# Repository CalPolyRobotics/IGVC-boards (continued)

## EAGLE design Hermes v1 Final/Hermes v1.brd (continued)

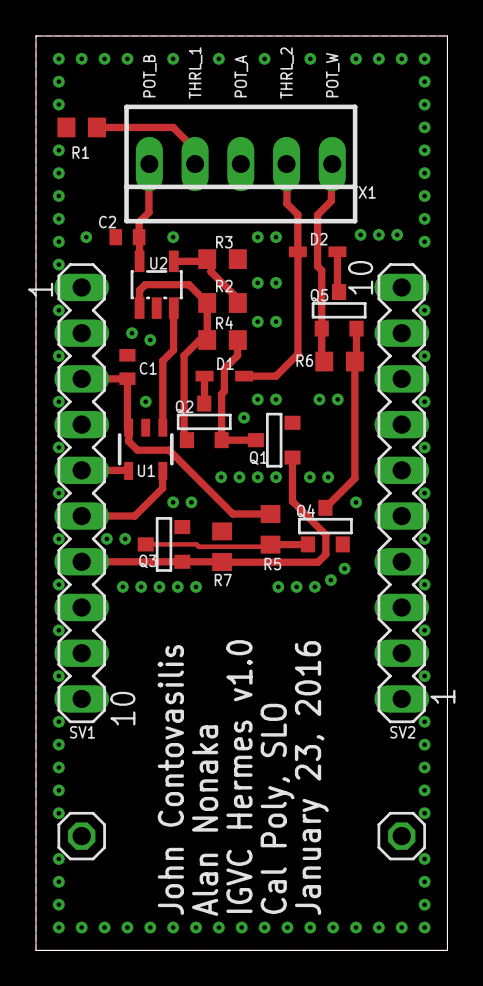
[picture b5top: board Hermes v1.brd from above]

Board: 2 copper layers, 22.9 x 50.8 mm, 23 parts (0 on the bottom side), 17 nets.

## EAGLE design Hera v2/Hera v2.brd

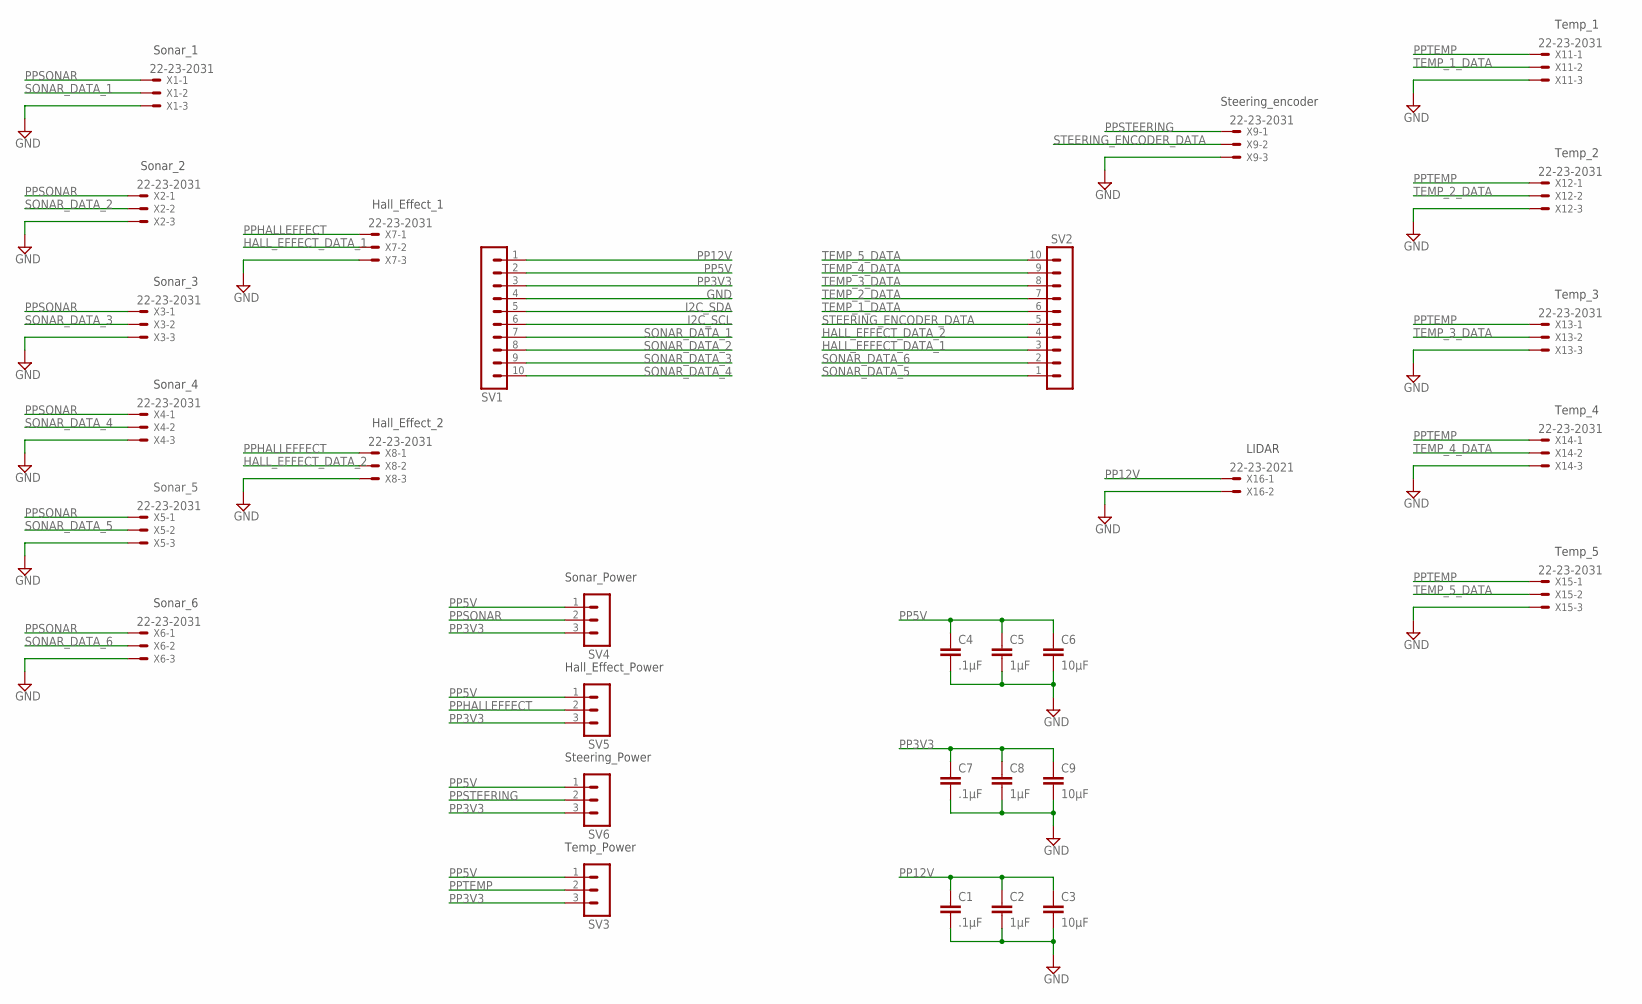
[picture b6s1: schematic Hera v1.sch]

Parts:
C1, C4, C7: .1µF; C0402; DIGI 490-5920-1-ND
C2, C5, C8: 1µF; C0603; DIGI 490-3897-1-ND
C3, C6, C9: 10µF; C1206; DIGI 490-5525-1-ND
SV1, SV2: MA10-1
SV3, SV4, SV5, SV6: MA03-1
X1, X2, X3, X4, X5, X6, X7, X8, X9, X11, X12, X13, X14, X15: 22-23-2031
X16: 22-23-2021

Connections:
GND: C1.2, C2.2, C3.2, C4.2, C5.2, C6.2, C7.2, C8.2, C9.2, SV1.4, X1.3, X2.3, X3.3, X4.3, X5.3, X6.3, X7.3, X8.3, X9.3, X11.3, X12.3, X13.3, X14.3, X15.3, X16.2
HALL_EFFECT_DATA_1: SV2.3, X7.2
HALL_EFFECT_DATA_2: SV2.4, X8.2
I2C_SCL: SV1.6
I2C_SDA: SV1.5
PP3V3: C7.1, C8.1, C9.1, SV1.3, SV3.3, SV4.3, SV5.3, SV6.3
PP5V: C4.1, C5.1, C6.1, SV1.2, SV3.1, SV4.1, SV5.1, SV6.1
PP12V: C1.1, C2.1, C3.1, SV1.1, X16.1
PPHALLEFFECT: SV5.2, X7.1, X8.1
PPSONAR: SV4.2, X1.1, X2.1, X3.1, X4.1, X5.1, X6.1
PPSTEERING: SV6.2, X9.1
PPTEMP: SV3.2, X11.1, X12.1, X13.1, X14.1, X15.1
SONAR_DATA_1: SV1.7, X1.2
SONAR_DATA_2: SV1.8, X2.2
SONAR_DATA_3: SV1.9, X3.2
SONAR_DATA_4: SV1.10, X4.2
SONAR_DATA_5: SV2.1, X5.2
SONAR_DATA_6: SV2.2, X6.2
STEERING_ENCODER_DATA: SV2.5, X9.2
TEMP_1_DATA: SV2.6, X11.2
TEMP_2_DATA: SV2.7, X12.2
TEMP_3_DATA: SV2.8, X13.2
TEMP_4_DATA: SV2.9, X14.2
TEMP_5_DATA: SV2.10, X15.2

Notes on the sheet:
Sonar_1
Sonar_2
Sonar_3
Sonar_4
Sonar_5
Sonar_6
Hall_Effect_1
Hall_Effect_2
Steering_encoder
Temp_1
Temp_2
Temp_3
Temp_4
Temp_5
LIDAR
Sonar_Power
Hall_Effect_Power
Steering_Power
Temp_Power

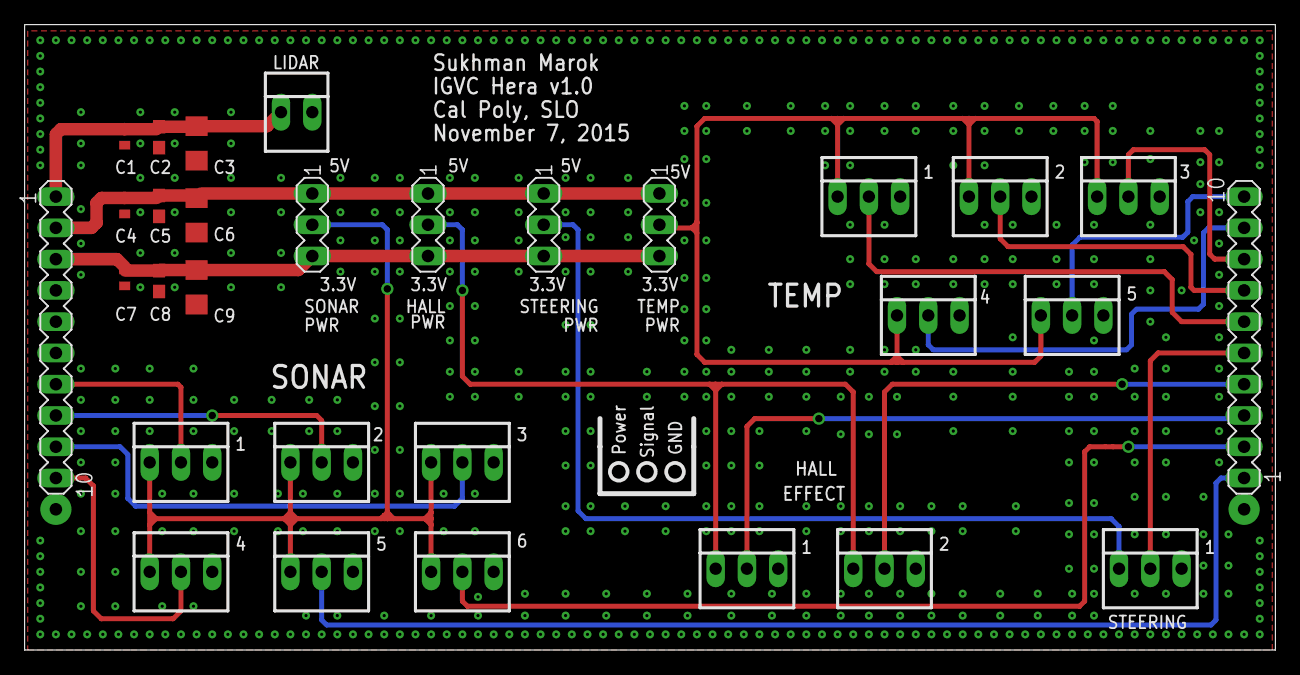
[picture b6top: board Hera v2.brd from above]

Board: 2 copper layers, 101.6 x 50.8 mm, 30 parts (0 on the bottom side), 22 nets.

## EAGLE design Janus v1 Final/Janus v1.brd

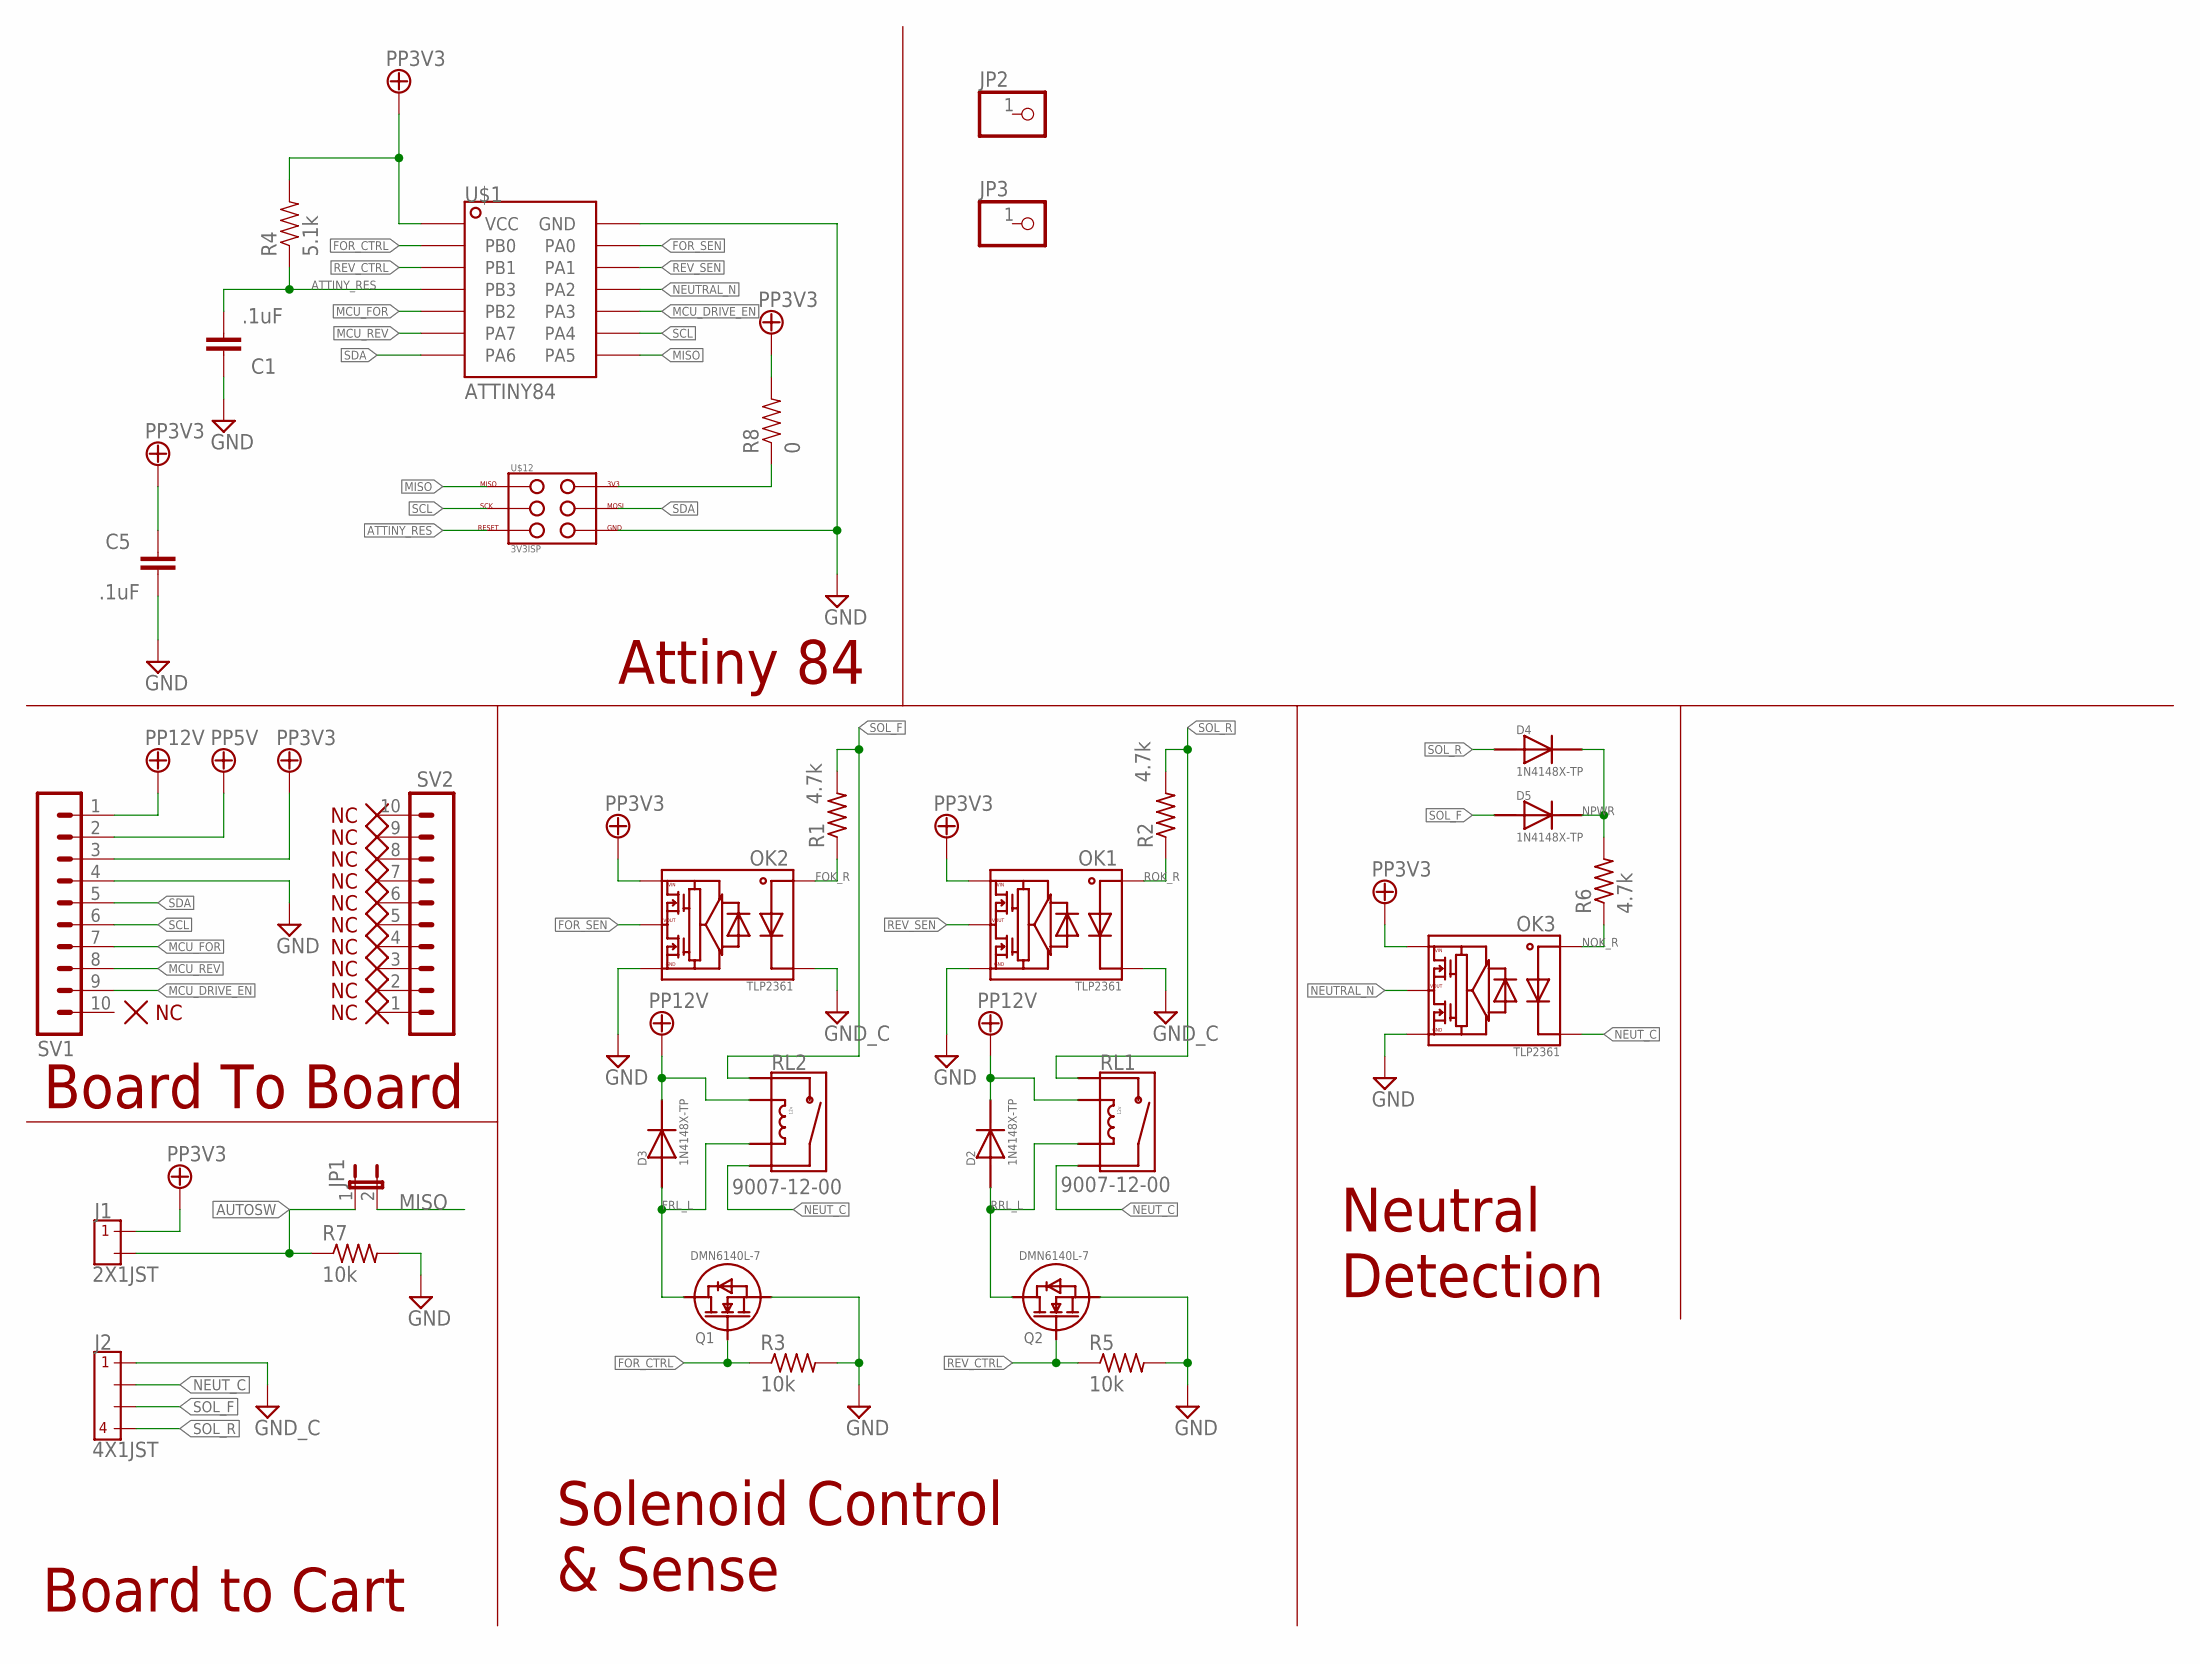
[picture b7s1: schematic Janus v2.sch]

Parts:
C1, C5: .1uF; C0603
D2, D3, D4, D5: 1N4148X-TP; SOD523_SC79
J1: 2X1JST; JST-2-PTH-VERT
J2: 4X1JST; JST-4-PTH-VERT
JP1: JP1E; JP1
JP2, JP3: PINHD-1X1; 1X01
OK1, OK2, OK3: TLP2361; SOIC-6-5
Q1, Q2: DMN6140L-7; SOT-23-3
R1, R2, R6: 4.7k; R0805
R3, R5, R7: 10k; R0603
R4: 5.1k; 0603-RES
R8: 0; 0603-RES
RL1, RL2: 9007-12-00; RELAY9007
SV1, SV2: MA10-1
U$1: ATTINY84; SOIC-14
U$12: 3V3ISP; 3X2SMD

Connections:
ATTINY_RES: C1.2, R4.1, U$1.P$4 (PB3), U$12.P$3
AUTOSW: J1.2, JP1.1, R7.1
FOK_R: OK2.P$1, R1.1
FOR_CTRL: Q1.P$1 (G), R3.1, U$1.P$2 (PB0)
FOR_SEN: OK2.P$5, U$1.P$13 (PA0)
FRL_L: D3.P$1, Q1.P$3 (D), RL2.P$3 (COILB)
GND: C1.1, C5.2, OK1.P$4, OK2.P$4, OK3.P$4, Q1.P$2 (S), Q2.P$2 (S), R3.2, R5.2, R7.2, SV1.4, U$1.P$14 (GND), U$12.P$4
GND_1: J2.1, OK1.P$3, OK2.P$3
MCU_DRIVE_EN: SV1.9, U$1.P$10 (PA3)
MCU_FOR: SV1.7, U$1.P$5 (PB2)
MCU_REV: SV1.8, U$1.P$6 (PA7)
MISO: JP1.2, U$1.P$8 (PA5), U$12.P$1
unnamed: R8.1, U$12.P$6
NEUTRAL_N: OK3.P$5, U$1.P$11 (PA2)
NEUT_C: J2.2, OK3.P$3, RL1.P$4 (SIGB), RL2.P$4 (SIGB)
NOK_R: OK3.P$1, R6.1
NPWR: D4.P$2, D5.P$2, R6.2
PP3V3: C5.1, J1.1, OK1.P$6, OK2.P$6, OK3.P$6, R4.2, R8.2, SV1.3, U$1.P$1 (VCC)
PP5V: SV1.2
PP12V: D2.P$2, D3.P$2, RL1.P$2 (COILA), RL2.P$2 (COILA), SV1.1
REV_CTRL: Q2.P$1 (G), R5.1, U$1.P$3 (PB1)
REV_SEN: OK1.P$5, U$1.P$12 (PA1)
ROK_R: OK1.P$1, R2.1
RRL_L: D2.P$1, Q2.P$3 (D), RL1.P$3 (COILB)
SCL: SV1.6, U$1.P$9 (PA4), U$12.P$2
SDA: SV1.5, U$1.P$7 (PA6), U$12.P$5
SOL_F: D5.P$1, J2.3, R1.2, RL2.P$1 (SIGA)
SOL_R: D4.P$1, J2.4, R2.2, RL1.P$1 (SIGA)

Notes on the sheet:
Attiny 84
Solenoid Control & Sense
Board To Board
Board to Cart
Neutral Detection

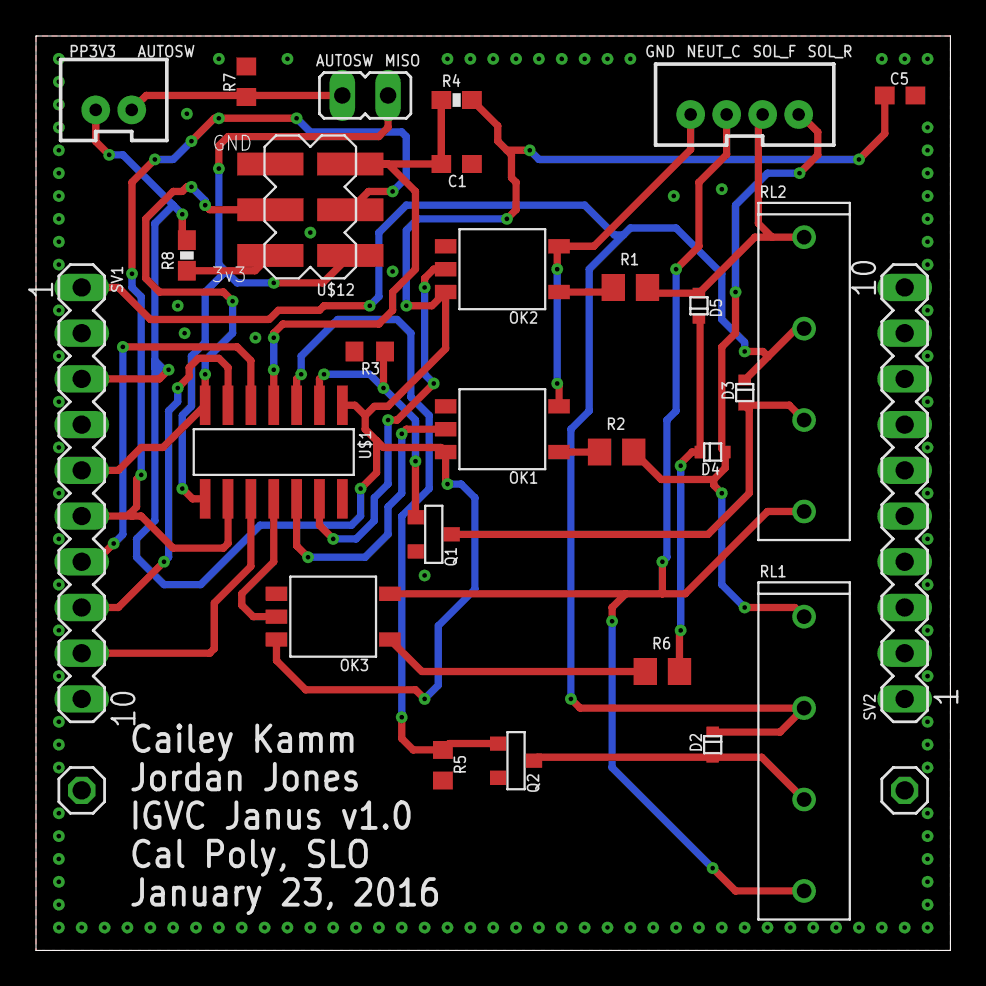
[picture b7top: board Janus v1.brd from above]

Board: 2 copper layers, 50.8 x 50.8 mm, 30 parts (0 on the bottom side), 27 nets.

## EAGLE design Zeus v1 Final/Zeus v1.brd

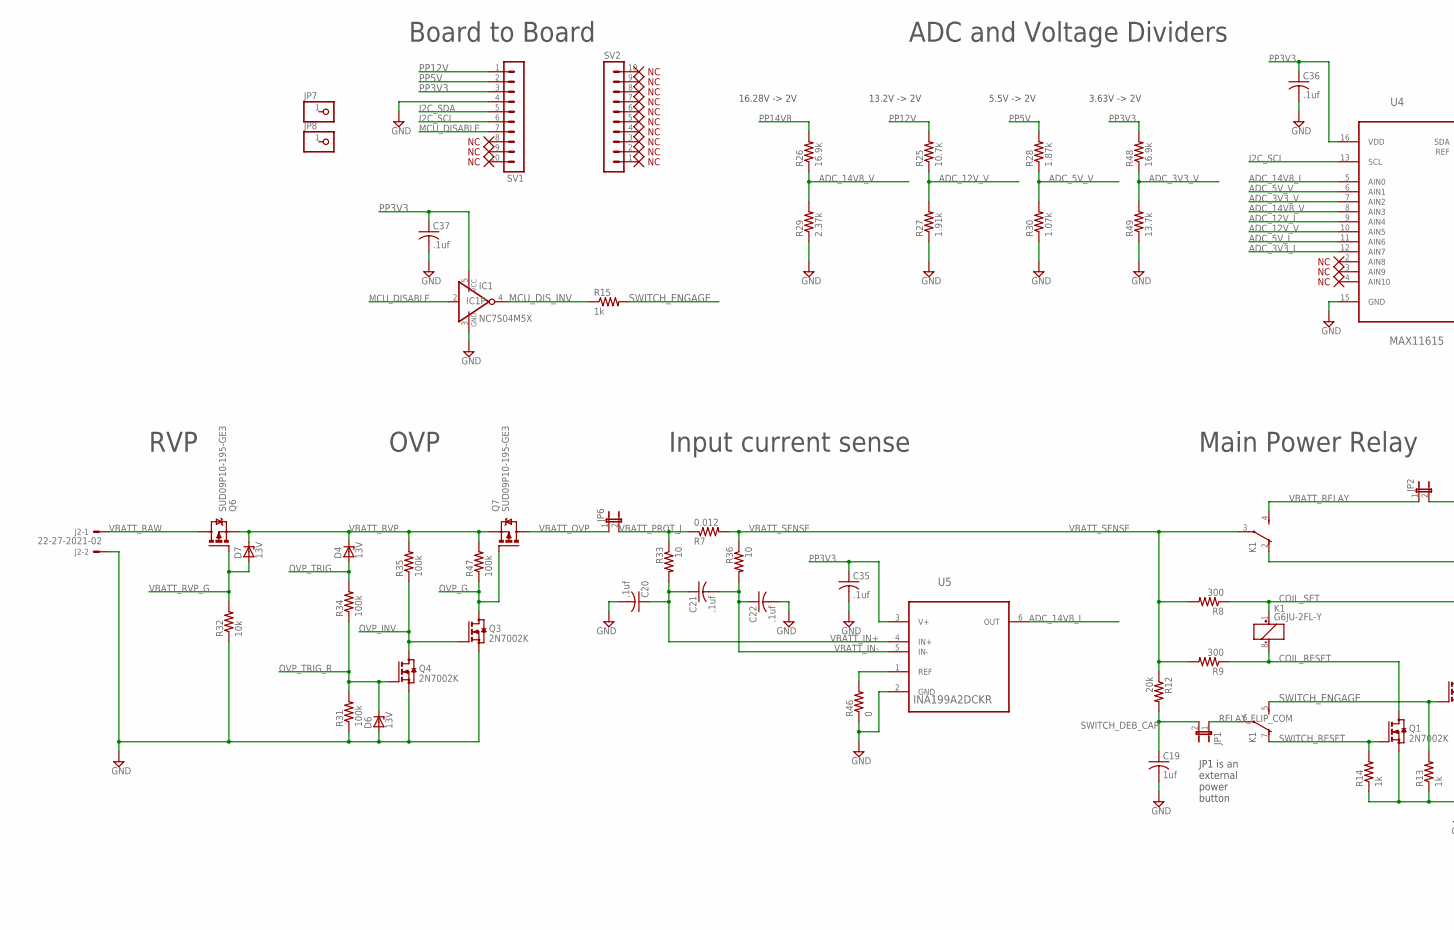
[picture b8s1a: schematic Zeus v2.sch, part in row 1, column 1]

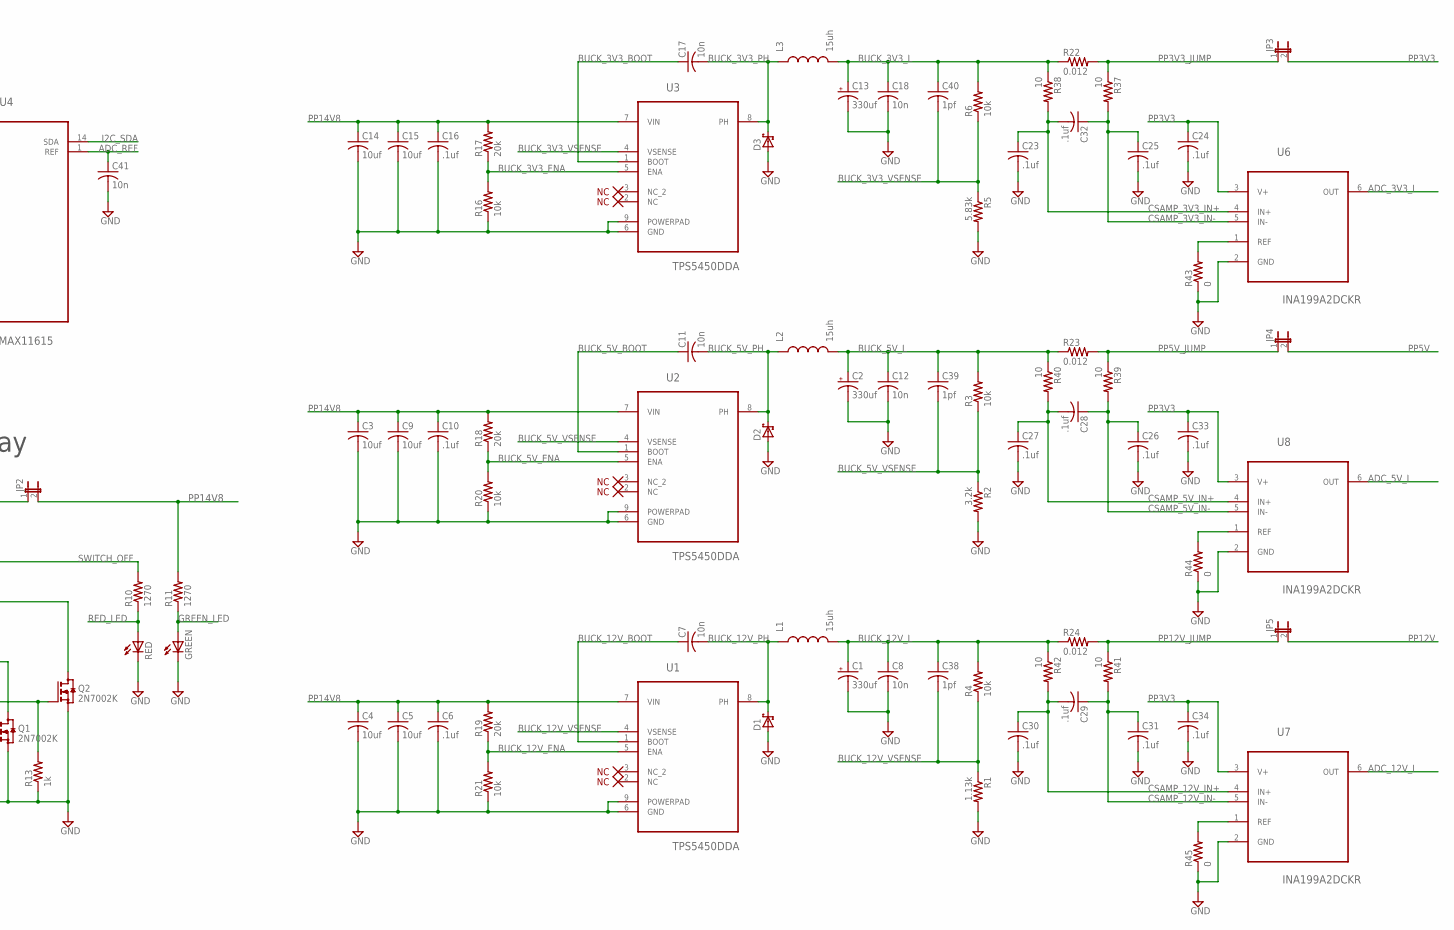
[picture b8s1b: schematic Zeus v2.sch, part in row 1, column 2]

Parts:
C1, C2, C13: 330uf; 153CLV-0605
C3, C4, C5, C9, C14, C15: 10uf; C1206
C6, C10, C16, C20, C21, C22, C23, C24, C25, C26, C27, C28, C29, C30, C31, C32, C33, C34, C35, C36, C37: .1uf; C0402
C7, C8, C11, C12, C17, C18, C41: 10n; C0402
C19: 1uf; C0603
C38, C39, C40: 1pf; C0402
D1, D2, D3: SCHOTTKY-DIODESMC; SMC
D4, D6, D7: 13V; SOT23
GREEN: LED_ESML0603; LED_SML0603
IC1: NC7S04M5X; SOT23-5
J2: 22-27-2021-02; 6410-02
JP1, JP2, JP3, JP4, JP5, JP6: JP1E; JP1
JP7, JP8: PINHD-1X1; 1X01
K1: G6JU-2FL-Y; G6J-2FL-Y
L1, L2, L3: 15uh; SUMIDA
Q1, Q2, Q3, Q4: 2N7002K; SOT23
Q6, Q7: SUD09P10-195-GE3; D-PAK_TO252AA
R1: 1.13k; R0603
R2: 3.2k; R0603
R3, R4, R6, R16, R20, R21, R32: 10k; R0603
R5: 5.83k; R0603
R7, R22, R23, R24: 0.012; R0805
R8, R9: 300; R0603
R10, R11: 1270; R0603
R12, R17, R18, R19: 20k; R0603
R13, R14, R15: 1k; R0603
R25: 10.7k; R0603
R26, R48: 16.9k; R0603
R27: 1.91k; R0603
R28: 1.87k; R0603
R29: 2.37k; R0603
R30: 1.07k; R0603
R31, R34, R35, R47: 100k; R0603
R33, R36, R37, R38, R39, R40, R41, R42: 10; R0603
R43, R44, R45, R46: 0; R0603
R49: 13.7k; R0603
RED: LED_ESML0603; LED_SML0603
SV1, SV2: MA10-1
U1, U2, U3: TPS5450DDA; SOIC127P600X170-9N
U4: MAX11615; SOP63P600X175-16N
U5, U6, U7, U8: INA199A2DCKR; SOT65P210X110-6N

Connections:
ADC_3V3_I: U4.12 (AIN7), U6.6 (OUT)
ADC_3V3_V: R48.1, R49.2, U4.7 (AIN2)
ADC_5V_I: U4.11 (AIN6), U8.6 (OUT)
ADC_5V_V: R28.1, R30.2, U4.6 (AIN1)
ADC_12V_I: U4.9 (AIN4), U7.6 (OUT)
ADC_12V_V: R25.1, R27.2, U4.10 (AIN5)
ADC_14V8_I: U4.5 (AIN0), U5.6 (OUT)
ADC_14V8_V: R26.1, R29.2, U4.8 (AIN3)
ADC_REF: C41.1, U4.1 (REF)
BUCK_3V3_BOOT: C17.1, U3.1 (BOOT)
BUCK_3V3_ENA: R16.2, R17.1, U3.5 (ENA)
BUCK_3V3_L: C13.+, C18.1, C40.1, L3.P$2 (2), R6.2, R22.1, R38.1
BUCK_3V3_PH: C17.2, D3.C, L3.P$1 (1), U3.8 (PH)
BUCK_3V3_VSENSE: C40.2, R5.1, R6.1, U3.4 (VSENSE)
BUCK_5V_BOOT: C11.1, U2.1 (BOOT)
BUCK_5V_ENA: R18.1, R20.2, U2.5 (ENA)
BUCK_5V_L: C2.+, C12.1, C39.1, L2.P$2 (2), R3.2, R23.1, R40.1
BUCK_5V_PH: C11.2, D2.C, L2.P$1 (1), U2.8 (PH)
BUCK_5V_VSENSE: C39.2, R2.1, R3.1, U2.4 (VSENSE)
BUCK_12V_BOOT: C7.1, U1.1 (BOOT)
BUCK_12V_ENA: R19.1, R21.2, U1.5 (ENA)
BUCK_12V_L: C1.+, C8.1, C38.1, L1.P$2 (2), R4.2, R24.1, R42.1
BUCK_12V_PH: C7.2, D1.C, L1.P$1 (1), U1.8 (PH)
BUCK_12V_VSENSE: C38.2, R1.1, R4.1, U1.4 (VSENSE)
COIL_RESET: K1.8 (-), Q1.3 (D), R9.1
COIL_SET: K1.1 (+), Q2.3 (D), R8.1
CSAMP_3V3_IN+: C23.1, C32.2, R38.2, U6.4 (IN+)
CSAMP_3V3_IN-: C25.1, C32.1, R37.2, U6.5 (IN-)
CSAMP_3V3_REF: R43.2, U6.1 (REF)
CSAMP_5V_IN+: C27.1, C28.2, R40.2, U8.4 (IN+)
CSAMP_5V_IN-: C26.1, C28.1, R39.2, U8.5 (IN-)
CSAMP_5V_REF: R44.2, U8.1 (REF)
CSAMP_12V_IN+: C29.2, C30.1, R42.2, U7.4 (IN+)
CSAMP_12V_IN-: C29.1, C31.1, R41.2, U7.5 (IN-)
CSAMP_12V_REF: R45.2, U7.1 (REF)
GND: C1.-, C2.-, C3.2, C4.2, C5.2, C6.2, C8.2, C9.2, C10.2, C12.2, C13.-, C14.2, C15.2, C16.2, C18.2, C19.2, C20.2, C22.2, C23.2, C24.2, C25.2, C26.2, C27.2, C30.2, C31.2, C33.2, C34.2, C35.2, C36.2, C37.2, C41.2, D1.A, D2.A, D3.A, D6.1 (A), GREEN.C, IC1.3 (GND), J2.2, Q1.2 (S), Q2.2 (S), Q3.2 (S), Q4.2 (S), R1.2, R2.2, R5.2, R13.1, R14.1, R16.1, R20.1, R21.1, R27.1, R29.1, R30.1, R31.1, R32.1, R43.1, R44.1, R45.1, R46.1, R49.1, RED.C, SV1.4, U1.6 (GND), U1.9 (POWERPAD), U2.6 (GND), U2.9 (POWERPAD), U3.6 (GND), U3.9 (POWERPAD), U4.15 (GND), U5.2 (GND), U6.2 (GND), U7.2 (GND), U8.2 (GND)
GREEN_LED: GREEN.A, R11.1
I2C_SCL: SV1.6, U4.13 (SCL)
I2C_SDA: SV1.5, U4.14 (SDA)
MCU_DISABLE: IC1.2 (I), SV1.7
MCU_DIS_INV: IC1.4 (O), R15.1
OPAMP_REF1: R46.2, U5.1 (REF)
OVP_G: Q3.3 (D), Q7.1 (G), R47.1
OVP_INV: Q3.1 (G), Q4.3 (D), R35.1
OVP_TRIG: D4.1 (A), R34.2
OVP_TRIG_R: D6.3 (C), Q4.1 (G), R31.2, R34.1
PP3V3: C24.1, C33.1, C34.1, C35.1, C36.1, C37.1, IC1.5 (VCC), JP3.2, R48.2, SV1.3, U4.16 (VDD), U5.3 (V+), U6.3 (V+), U7.3 (V+), U8.3 (V+)
PP3V3_JUMP: JP3.1, R22.2, R37.1
PP5V: JP4.2, R28.2, SV1.2
PP5V_JUMP: JP4.1, R23.2, R39.1
PP12V: JP5.2, R25.2, SV1.1
PP12V_JUMP: JP5.1, R24.2, R41.1
PP14V8: C3.1, C4.1, C5.1, C6.1, C9.1, C10.1, C14.1, C15.1, C16.1, JP2.2, R11.2, R17.2, R18.2, R19.2, R26.2, U1.7 (VIN), U2.7 (VIN), U3.7 (VIN)
RED_LED: R10.1, RED.A
RELAY_FLIP_COM: JP1.1, K1.6
SWITCH_DEB_CAP: C19.1, JP1.2, R12.2
SWITCH_ENGAGE: K1.5 (S), Q2.1 (G), R13.2, R15.2
SWITCH_OFF: K1.2 (O), R10.2
SWITCH_RESET: K1.7 (O), Q1.1 (G), R14.2
VBATT_IN+: C20.1, C21.1, R33.2, U5.4 (IN+)
VBATT_IN-: C21.2, C22.1, R36.2, U5.5 (IN-)
VBATT_OVP: JP6.1, Q7.4 (D)
VBATT_PROT_J: JP6.2, R7.1, R33.1
VBATT_RAW: J2.1, Q6.4 (D)
VBATT_RELAY: JP2.1, K1.4 (S)
VBATT_RVP: D4.3 (C), D7.3 (C), Q6.3 (S), Q7.3 (S), R35.2, R47.2
VBATT_RVP_G: D7.1 (A), Q6.1 (G), R32.2
VBATT_SENSE: K1.3, R7.2, R8.2, R9.2, R12.1, R36.1

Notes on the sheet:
RVP
Input current sense
JP1 is an external power button
Board to Board
Main Power Relay
ADC and Voltage Dividers
16.28V -> 2V
5.5V -> 2V
13.2V -> 2V
OVP
3.63V -> 2V

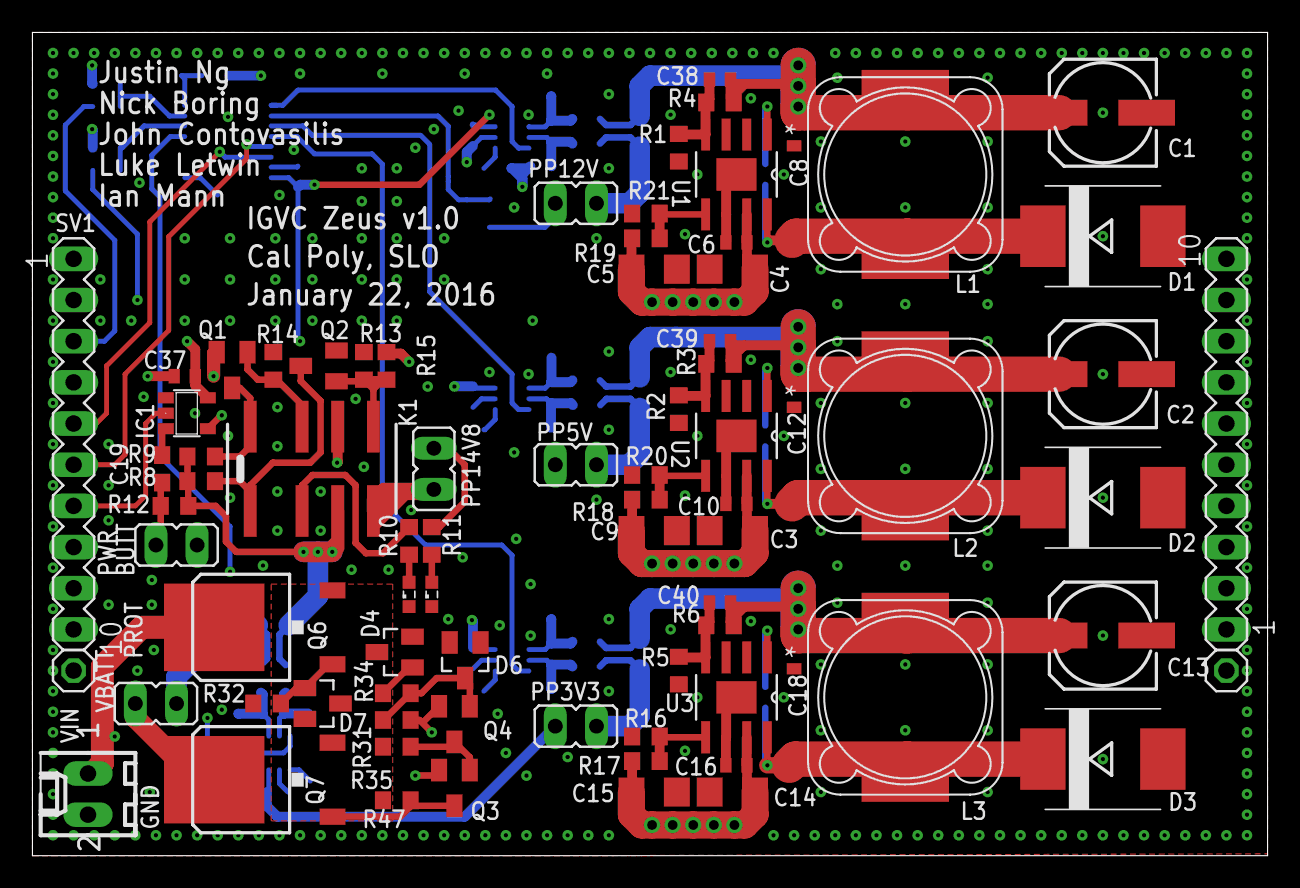
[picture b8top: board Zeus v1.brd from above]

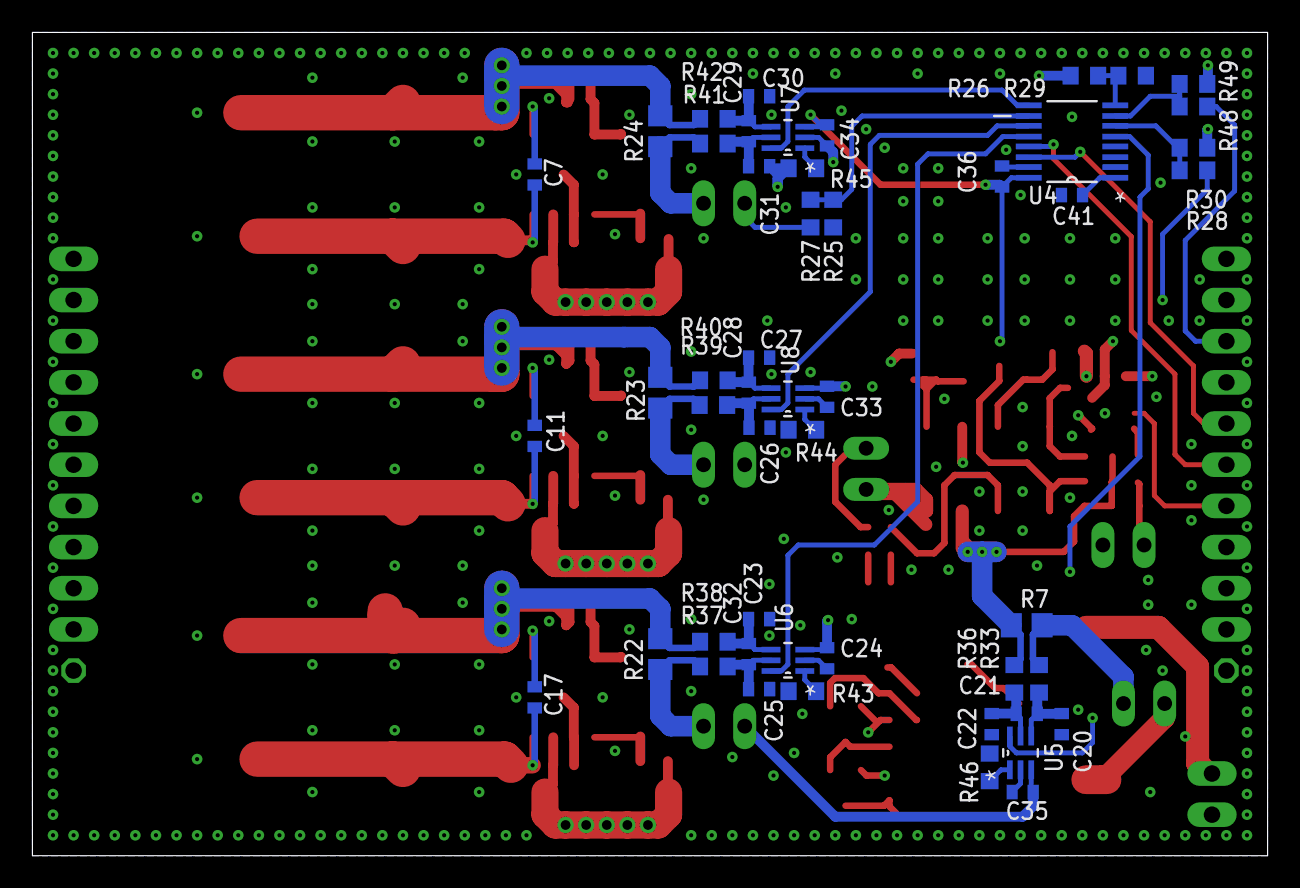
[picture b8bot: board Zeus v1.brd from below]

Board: 4 copper layers, 76.2 x 50.8 mm, 128 parts (50 on the bottom side), 68 nets.

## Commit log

2016-10-07 Initial upload
2016-10-07 Modified gitignore to allow .lib. Updated README
2016-10-07 Fixed readme formatting.
2016-10-07 Fixed .gitignore .lib to .lbr
2016-10-07 Added NC.lbr
2016-10-08 Removed extra new line
2016-10-09 added Dionysus incomplete schematic
2016-11-12 moved connector on iris
2016-11-12 updated hermes
2016-11-21 Preliminary push of Hephastus V1_5. Values for specific components on A4957 chip have yet to be settled, and connectors (board-board, board-cart, board-motor) have yet to be selected. "Structure" of 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
2016-11-21 Added the library containing (layout incomplete) components for the Hephaestus board.
2016-12-03 Schematic for Hephaestus V1_5 is essentially complete, need to select C2 and C1 values
2017-01-14 I updated Olympus by changing the USB pins, the GPIO LEDS, and updated the Hermes, Hephaestus, and Iris pinouts and connections to the microcontroller. I also added pull down resistors on theLEDS.
2017-01-21 Added golf cart master schematic
2017-01-21 Small changes and updates to the catch-diodes and P/N
2017-01-21 Updated NMOS/PMOS/Catch Diodes to properly specc, added voltage divider / buffer between current transducer and ADC.
2017-01-22 fixed hermes issues
2017-01-22 fixed more hermes things
2017-01-28 Most recent revision; added voltage divider / buffer to make current transducers compatible with ADC input voltage.
2017-01-28 Fixed layouts and pin ordering / connections.
2017-02-04 Hopefully the resistors and capacitors are up to spec and I can move on.
2017-02-17 Most recent changes (gate logic, decoupling capacitors, everything hopefully properly specced) hopefully
